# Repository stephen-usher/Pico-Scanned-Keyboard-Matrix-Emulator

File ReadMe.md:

This is a generic scanned keyboard matrix emulation board based upon a Raspberry Pi Pico.

It supports any scanned keyboard matrix which has up to 8 scan lines (outputs from the computer) and 12 sense lines (inputs to the computer).

The board itself is really just a Pico interface board with 8 TTL compatible inputs to the GPIO and 12 TTL compatible outputs with an RS232 compatible interface to the default UART. The 8 and 12 pin ports are contiguous ranges on the Pico allowing PIO operations as a bus. All the keyboard matrix magic happens in software. It's using 74LVC244 chips to act as step-down voltage converted on the input and the 74LS244 as a step-up on the output.

The initial firmware supports the Sinclair QL but I will later probably add the Memotech MTX Series and maybe ZX Spectrum and ZX81.

To use the board with a USB keyboard you will need to add a USB OTG (On The Go) adapter cable and set the Pico SDK to use the serial port for stdio so as to use the TinyUSB library.

Note: Because I didn't realise that the Pico doesn't drive the VBUS power line when powered from the VSYS line a bodge wire will be needed to bridge between the two pins on the Pico otherwise the output 74LS244 doesn't get power.

Note 2: If you only need 8 sense lines (such as for the Sinclair QL) and you don't need the RS232 port then you only need to install U1 and U3 buffer chips and not U2 (74VLC244) or U4 (MAX232) you also don't need to fit the DB9 socket or the two electrolytic caps. In this minimal configuration you only need +5V and GND to power the board.

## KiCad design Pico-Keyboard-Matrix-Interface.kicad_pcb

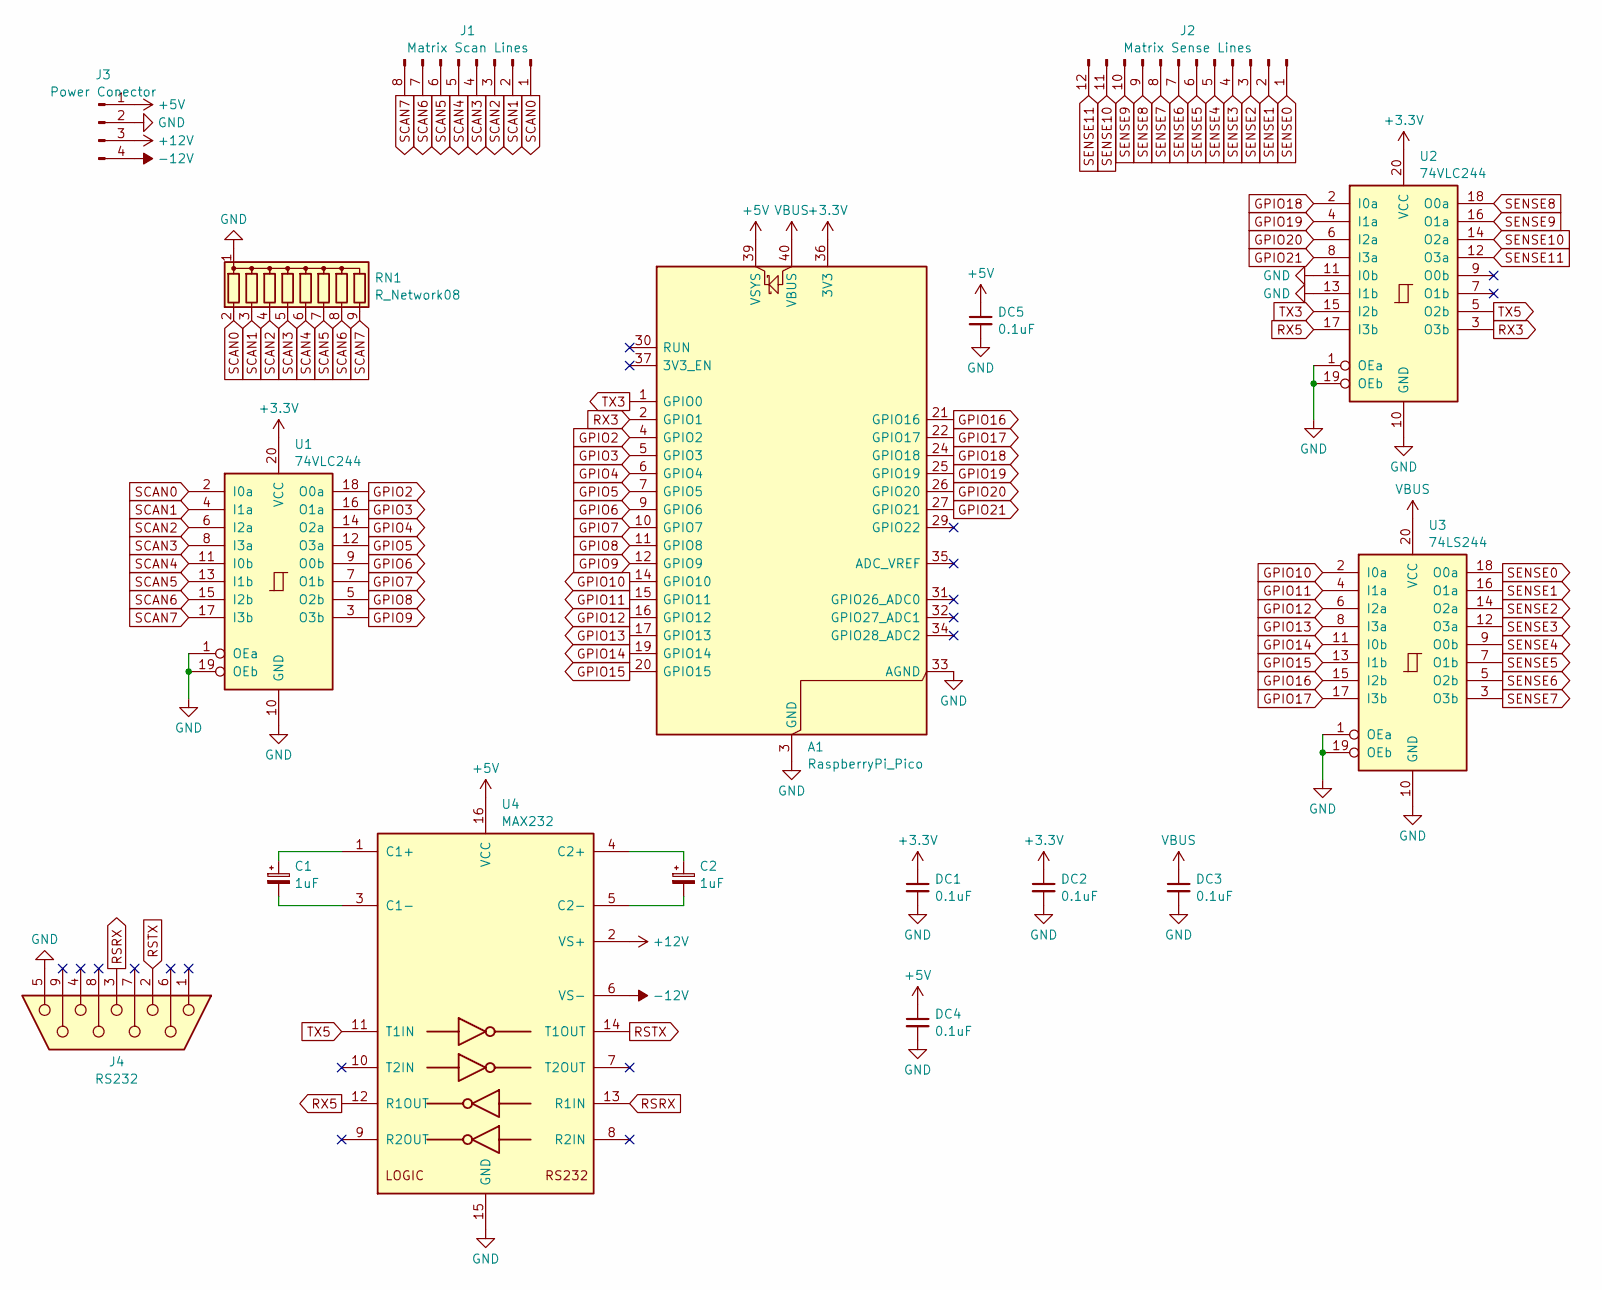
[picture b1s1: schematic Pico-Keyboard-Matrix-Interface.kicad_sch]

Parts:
A1: RaspberryPi_Pico; RaspberryPi_Pico_Common_Unspecified
C1, C2: 1uF; CP_Radial_D4.0mm_P2.00mm
DC1, DC2, DC3, DC4, DC5: 0.1uF; C_0805_2012Metric_Pad1.18x1.45mm_HandSolder
J1: Matrix Scan Lines; PinHeader_1x08_P2.54mm_Vertical
J2: Matrix Sense Lines; PinHeader_1x12_P2.54mm_Vertical
J3: Power Conector; PinHeader_1x04_P2.54mm_Horizontal
J4: RS232; DSUB-9_Socket_Horizontal_P2.77x2.84mm_EdgePinOffset9.40mm
RN1: R_Network08; R_Array_SIP9
U1, U2: 74VLC244; DIP-20_W7.62mm_Socket
U3: 74LS244; DIP-20_W7.62mm_Socket
U4: MAX232; DIP-16_W7.62mm_Socket

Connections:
+3.3V: A1.36 (3V3), DC1.1, DC2.1, U1.20 (VCC), U2.20 (VCC)
+5V: A1.39 (VSYS), DC4.1, DC5.1, J3.1, U4.16 (VCC)
+12V: J3.3, U4.2 (VS+)
-12V: J3.4, U4.6 (VS-)
GND: A1.3 (GND), A1.8 (GND), A1.13 (GND), A1.18 (GND), A1.23 (GND), A1.28 (GND), A1.33 (AGND), A1.38 (GND), DC1.2, DC2.2, DC3.2, DC4.2, DC5.2, J3.2, J4.5, RN1.1 (common), U1.1 (OEa), U1.10 (GND), U1.19 (OEb), U2.1 (OEa), U2.10 (GND), U2.11 (I0b), U2.13 (I1b), U2.19 (OEb), U3.1 (OEa), U3.10 (GND), U3.19 (OEb), U4.15 (GND)
GPIO2: A1.4 (GPIO2), U1.18 (O0a)
GPIO3: A1.5 (GPIO3), U1.16 (O1a)
GPIO4: A1.6 (GPIO4), U1.14 (O2a)
GPIO5: A1.7 (GPIO5), U1.12 (O3a)
GPIO6: A1.9 (GPIO6), U1.9 (O0b)
GPIO7: A1.10 (GPIO7), U1.7 (O1b)
GPIO8: A1.11 (GPIO8), U1.5 (O2b)
GPIO9: A1.12 (GPIO9), U1.3 (O3b)
GPIO10: A1.14 (GPIO10), U3.2 (I0a)
GPIO11: A1.15 (GPIO11), U3.4 (I1a)
GPIO12: A1.16 (GPIO12), U3.6 (I2a)
GPIO13: A1.17 (GPIO13), U3.8 (I3a)
GPIO14: A1.19 (GPIO14), U3.11 (I0b)
GPIO15: A1.20 (GPIO15), U3.13 (I1b)
GPIO16: A1.21 (GPIO16), U3.15 (I2b)
GPIO17: A1.22 (GPIO17), U3.17 (I3b)
GPIO18: A1.24 (GPIO18), U2.2 (I0a)
GPIO19: A1.25 (GPIO19), U2.4 (I1a)
GPIO20: A1.26 (GPIO20), U2.6 (I2a)
GPIO21: A1.27 (GPIO21), U2.8 (I3a)
unnamed: C1.1, U4.1 (C1+)
unnamed: C1.2, U4.3 (C1-)
unnamed: C2.1, U4.4 (C2+)
unnamed: C2.2, U4.5 (C2-)
RSRX: J4.3, U4.13 (R1IN)
RSTX: J4.2, U4.14 (T1OUT)
RX3: A1.2 (GPIO1), U2.3 (O3b)
RX5: U2.17 (I3b), U4.12 (R1OUT)
SCAN0: J1.1, RN1.2 (R1), U1.2 (I0a)
SCAN1: J1.2, RN1.3 (R2), U1.4 (I1a)
SCAN2: J1.3, RN1.4 (R3), U1.6 (I2a)
SCAN3: J1.4, RN1.5 (R4), U1.8 (I3a)
SCAN4: J1.5, RN1.6 (R5), U1.11 (I0b)
SCAN5: J1.6, RN1.7 (R6), U1.13 (I1b)
SCAN6: J1.7, RN1.8 (R7), U1.15 (I2b)
SCAN7: J1.8, RN1.9 (R8), U1.17 (I3b)
SENSE0: J2.1, U3.18 (O0a)
SENSE1: J2.2, U3.16 (O1a)
SENSE2: J2.3, U3.14 (O2a)
SENSE3: J2.4, U3.12 (O3a)
SENSE4: J2.5, U3.9 (O0b)
SENSE5: J2.6, U3.7 (O1b)
SENSE6: J2.7, U3.5 (O2b)
SENSE7: J2.8, U3.3 (O3b)
SENSE8: J2.9, U2.18 (O0a)
SENSE9: J2.10, U2.16 (O1a)
SENSE10: J2.11, U2.14 (O2a)
SENSE11: J2.12, U2.12 (O3a)
TX3: A1.1 (GPIO0), U2.15 (I2b)
TX5: U2.5 (O2b), U4.11 (T1IN)
VBUS: A1.40 (VBUS), DC3.1, U3.20 (VCC)

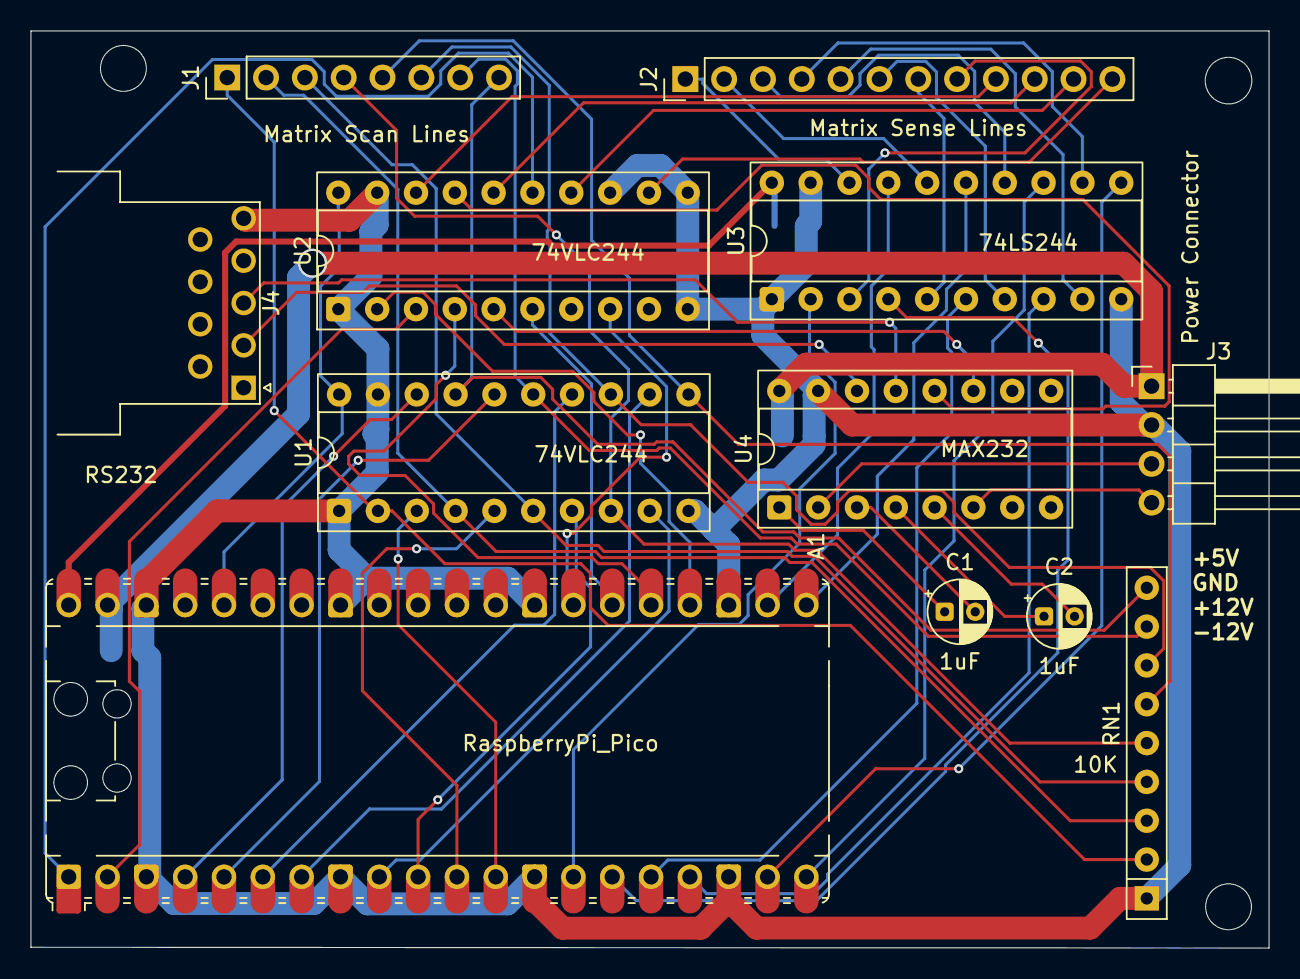
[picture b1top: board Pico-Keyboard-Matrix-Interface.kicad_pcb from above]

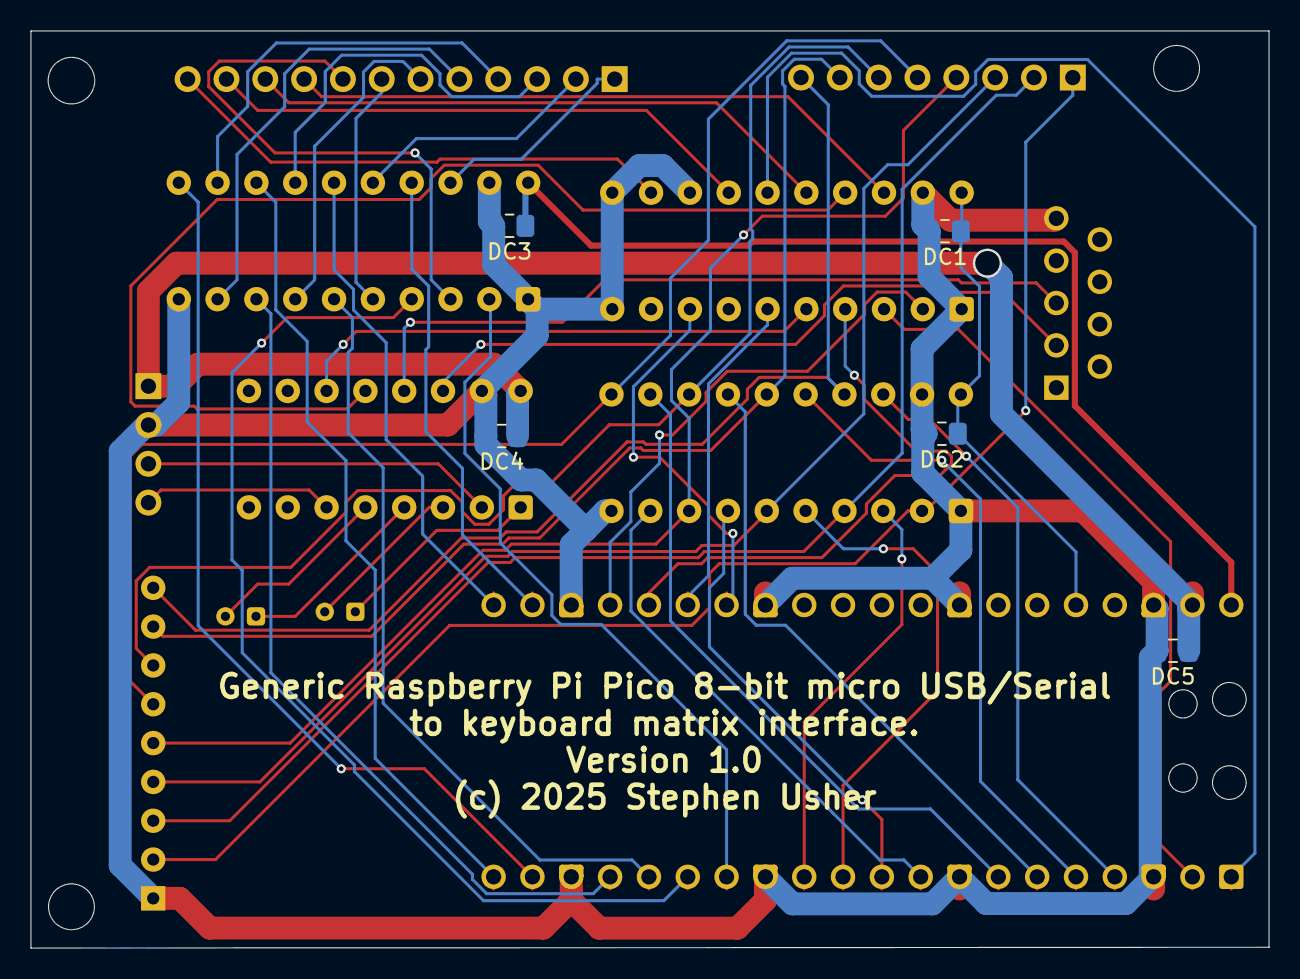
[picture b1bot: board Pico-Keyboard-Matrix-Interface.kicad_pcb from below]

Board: 2 copper layers, 81.0 x 60.0 mm, 17 parts (5 on the bottom side), 56 nets.

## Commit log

2025-08-04 Updated Readme files
2025-08-04 Added binary
2025-08-10 Fixed typo in the USB keycode translation tables for up and down cursor keys.
2025-08-10 Update Keyboard-Matrix.pdf
    Made actually readable
2025-09-12 Typo in QL firmware keycodes.c
    Fixed typo which prevented the main keyboard '9' from working.
2025-09-26 USB keyboard code re-written
    The code for dealing with the USB keyboard reading has been re-written to allow roll-over.
    The original code just read the first entry in the USB keyboard report but I found that on a keyboard with proper key switches key presses would be missed due to a previous key not being released in 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
    Reading multiple keys using the tinyusb library is made more complex by the library not returning how many keys are currently pressed and the report also doesn't hold them in chronological order or e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
    This code still isn't able to report multiple keys pressed at the same time to the

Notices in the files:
Pico-Keyboard-Matrix-Interface.kicad_pcb:
(c) 2025 Stephen Usher
